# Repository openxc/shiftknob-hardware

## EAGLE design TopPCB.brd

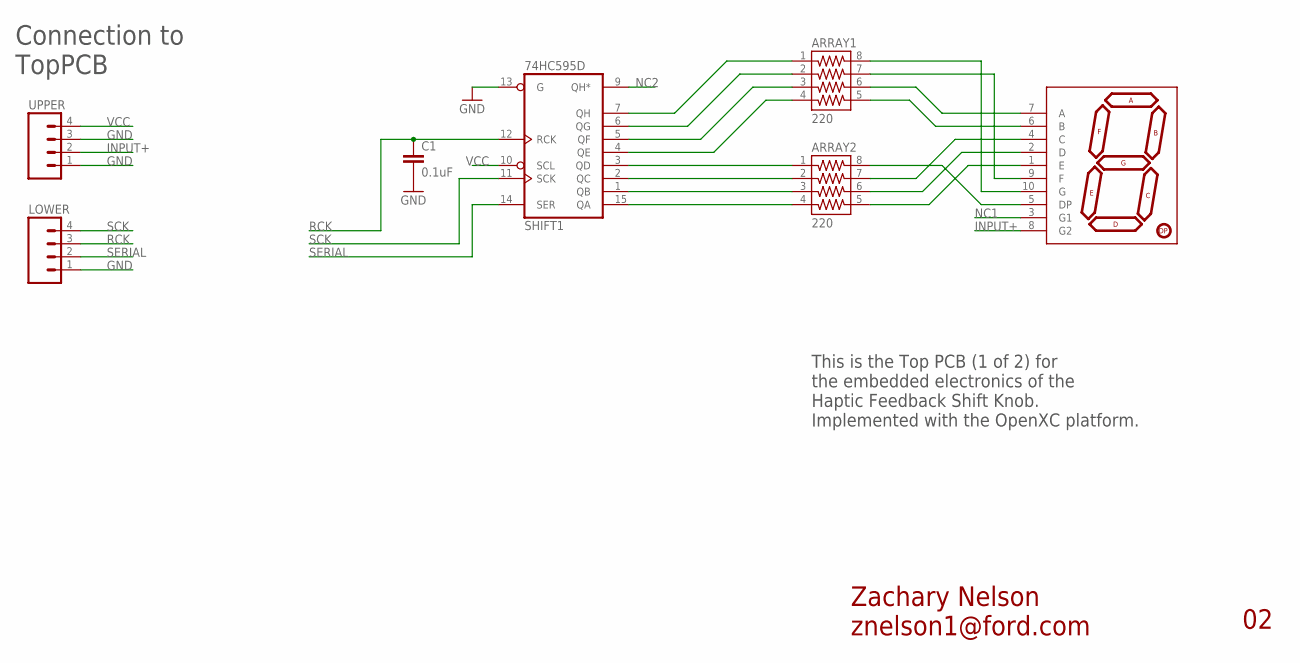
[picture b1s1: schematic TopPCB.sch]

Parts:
7SEGMENT: 7-SEGMENT-DISPLAY-1"-RED; 7-SEGMENT-1"PTH
ARRAY1, ARRAY2: 220; 744-8
C1: 0.1uF; 0402-CAP
LOWER: M04PTH; 1X04
SHIFT1: 74HC595D; SO16
UPPER: M04PTH; 1X04

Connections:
GND: C1.2, LOWER.1, SHIFT1.8 (GND), SHIFT1.13 (G), UPPER.1, UPPER.3
INPUT+: 7SEGMENT.8 (G2), UPPER.2
unnamed: 7SEGMENT.5 (DP), ARRAY2.8
unnamed: ARRAY2.3, SHIFT1.1 (QB)
unnamed: 7SEGMENT.1 (E), ARRAY2.5
unnamed: ARRAY2.2, SHIFT1.2 (QC)
unnamed: ARRAY2.1, SHIFT1.3 (QD)
unnamed: 7SEGMENT.4 (C), ARRAY2.7
unnamed: 7SEGMENT.6 (B), ARRAY1.5
unnamed: ARRAY2.4, SHIFT1.15 (QA)
unnamed: ARRAY1.4, SHIFT1.4 (QE)
unnamed: ARRAY1.3, SHIFT1.5 (QF)
unnamed: ARRAY1.2, SHIFT1.6 (QG)
unnamed: ARRAY1.1, SHIFT1.7 (QH)
unnamed: 7SEGMENT.7 (A), ARRAY1.6
unnamed: 7SEGMENT.9 (F), ARRAY1.7
unnamed: 7SEGMENT.10 (G), ARRAY1.8
unnamed: 7SEGMENT.2 (D), ARRAY2.6
NC1: 7SEGMENT.3 (G1)
NC2: SHIFT1.9 (QH*)
RCK: C1.1, LOWER.3, SHIFT1.12 (RCK)
SCK: LOWER.4, SHIFT1.11 (SCK)
SERIAL: LOWER.2, SHIFT1.14 (SER)
VCC: SHIFT1.10 (SCL), SHIFT1.16 (VCC), UPPER.4

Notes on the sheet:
Zachary Nelson znelson1@ford.com
This is the Top PCB (1 of 2) for the embedded electronics of the Haptic Feedback Shift Knob. Implemented with the OpenXC platform.
Connection to TopPCB

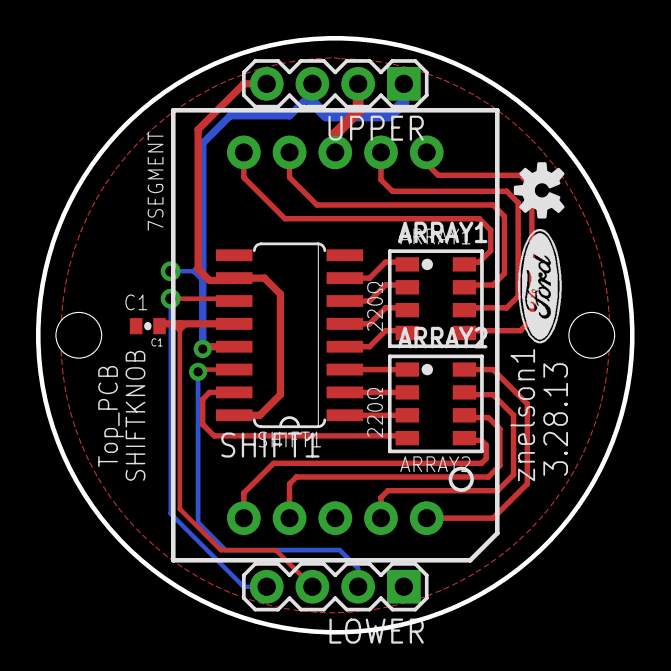
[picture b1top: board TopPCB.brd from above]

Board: 2 copper layers, 33.0 x 33.0 mm, 10 parts (1 on the bottom side), 22 nets.

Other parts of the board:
U$1, U$2: OSHW-LOGOS; OSHW-LOGO-S
U$3: DOCFIELD

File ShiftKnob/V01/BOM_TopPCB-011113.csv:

"Part";"Value";"Device";"Package";"Description";"";
"C1";"0.1uF";"CAP0402-CAP";"0402-CAP";"Capacitor";"";
"IC1";"74HC595D";"74HC595D";"SO16";"8-bit SHIFT REGISTER, output latch";"";
"JP1";"6 PIN 90degree Header";"M06POGOPIN_HOLES_ONLY";"1X06_HOLES_ONLY";"Header 6";"";
"RN1";"220";"744-8";"744-8";"CTS 744 Series";"";
"RN2";"220";"744-8";"744-8";"CTS 744 Series";"";
"U$1";"7-SEGMENT-DISPLAY-1"-RED";"7-SEGMENT-DISPLAY-1"-RED";"7-SEGMENT-1"PTH";"7-Segment Display 1" Red (COM-08546)";"";

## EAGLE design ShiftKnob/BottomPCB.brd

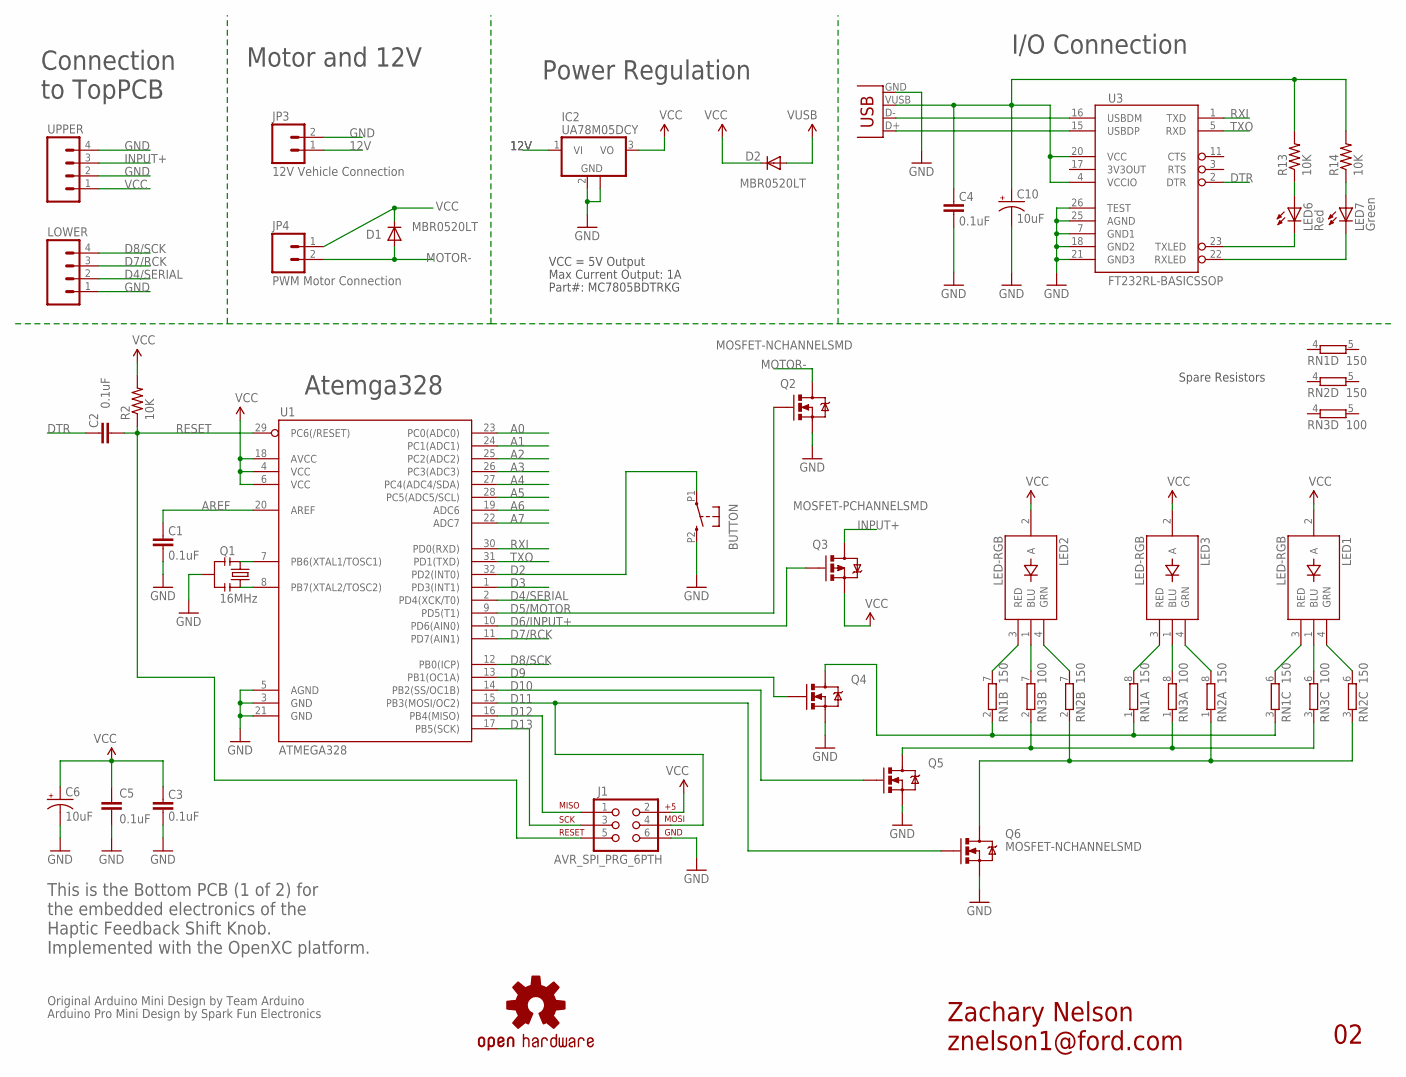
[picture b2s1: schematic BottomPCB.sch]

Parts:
BUTTON: BUTTON_EDGE
C1, C2, C3, C4, C5: 0.1uF; 0402-CAP
C6, C10: 10uF; EIA3216
D1, D2: MBR0520LT; SOD123
IC2: UA78M05DCY; SOT223
J1: AVR_SPI_PRG_6PTH; 2X3
JP3: 12V Vehicle Connection; 1X02
JP4: PWM Motor Connection; JST-2-SMD
LED1, LED2, LED3: LED-RGB; LED-RGB_SMD-RIGHTANGLE
LED6: Red; LED-0603
LED7: Green; LED-0603
LOWER: M04PTH; 1X04
Q1: 16MHz; RESONATOR-SMD
Q2, Q4, Q5, Q6: MOSFET-NCHANNELSMD; SOT23-3
Q3: MOSFET-PCHANNELSMD; SOT23-3
R2, R13, R14: 10K; 0402-RES
RN1, RN2: 150; EXBS8V
RN3: 100; EXBS8V
U1: ATMEGA328; TQFP32-08
U3: FT232RL-BASICSSOP; SSOP28DB
U6: USB-MINI-B_VERTICAL
U$3: OSHW-LOGOS; OSHW-LOGO-S
UPPER: M04PTH; 1X04

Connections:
12V: IC2.1 (VI), JP3.1
A0: U1.23 (PC0(ADC0))
A1: U1.24 (PC1(ADC1))
A2: U1.25 (PC2(ADC2))
A3: U1.26 (PC3(ADC3))
A4: U1.27 (PC4(ADC4/SDA))
A5: U1.28 (PC5(ADC5/SCL))
A6: U1.19 (ADC6)
A7: U1.22 (ADC7)
AREF: C1.2, U1.20 (AREF)
D2: BUTTON.P1 (1), U1.32 (PD2(INT0))
D3: U1.1 (PD3(INT1))
D4/SERIAL: LOWER.2, U1.2 (PD4(XCK/T0))
D5/MOTOR: Q2.1 (G), U1.9 (PD5(T1))
D6/INPUT+: Q3.1 (G), U1.10 (PD6(AIN0))
D7/RCK: LOWER.3, U1.11 (PD7(AIN1))
D8/SCK: LOWER.4, U1.12 (PB0(ICP))
D9: Q4.3 (D), RN1.1, RN1.2 (1), RN1.3 (1)
D10: Q5.3 (D), RN3.1, RN3.2 (1), RN3.3 (1)
D11: Q6.3 (D), RN2.1, RN2.2 (1), RN2.3 (1)
D12: J1.1, U1.16 (PB4(MISO))
D13: J1.3, U1.17 (PB5(SCK))
DTR: C2.2, U3.2 (DTR)
GND: BUTTON.P2 (2), C1.1, C3.1, C4.1, C5.2, C6.C (-), C10.C (-), IC2.2 (GND), IC2.4 (GND), J1.6, JP3.2, LOWER.1, Q1.2, Q2.2 (S), Q4.2 (S), Q5.2 (S), Q6.2 (S), U1.3 (GND), U1.5 (AGND), U1.21 (GND), U3.7 (GND1), U3.18 (GND2), U3.21 (GND3), U3.25 (AGND), U3.26 (TEST), U6.GND, UPPER.2, UPPER.4
INPUT+: Q3.3 (D), UPPER.3
MOTOR-: D1.A, JP4.2 (1), Q2.3 (D)
unnamed: Q1.1, U1.8 (PB7(XTAL2/TOSC2))
unnamed: Q1.3, U1.7 (PB6(XTAL1/TOSC1))
unnamed: LED2.3 (RED), RN1.7 (2)
unnamed: LED2.4 (GRN), RN2.7 (2)
unnamed: LED3.3 (RED), RN1.8 (2)
unnamed: LED1.1 (BLU), RN3.6 (2)
unnamed: LED3.4 (GRN), RN2.8 (2)
unnamed: LED1.3 (RED), RN1.6 (2)
unnamed: LED1.4 (GRN), RN2.6 (2)
unnamed: Q4.1 (G), U1.13 (PB1(OC1A))
unnamed: Q5.1 (G), U1.14 (PB2(SS/OC1B))
unnamed: J1.4, Q6.1 (G), U1.15 (PB3(MOSI/OC2))
unnamed: LED2.1 (BLU), RN3.7 (2)
unnamed: LED3.1 (BLU), RN3.8 (2)
unnamed: U3.15 (USBDP), U6.D+
unnamed: U3.16 (USBDM), U6.D-
unnamed: LED6.A, R13.1
unnamed: LED7.A, R14.1
RESET: C2.1, J1.5, R2.1, U1.29 (PC6(/RESET))
RXI: U1.30 (PD0(RXD)), U3.1 (TXD)
RXLED1: LED7.C, U3.22 (RXLED)
TXLED1: LED6.C, U3.23 (TXLED)
TXO: U1.31 (PD1(TXD)), U3.5 (RXD)
VCC: C3.2, C5.1, C6.A (+), D1.C, D2.C, IC2.3 (VO), J1.2, JP4.1 (2), LED1.2 (A), LED2.2 (A), LED3.2 (A), Q3.2 (S), R2.2, U1.4 (VCC), U1.6 (VCC), U1.18 (AVCC), UPPER.1
VUSB: C4.2, C10.A (+), D2.A, R13.2, R14.2, U3.4 (VCCIO), U3.20 (VCC), U6.VUSB (VBUS)

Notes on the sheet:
Zachary Nelson znelson1@ford.com
Original Arduino Mini Design by Team Arduino
Arduino Pro Mini Design by Spark Fun Electronics
Max Current Output: 1A
VCC = 5V Output
Part#: MC7805BDTRKG
Power Regulation
I/O Connection
Motor and 12V
Atemga328
Connection to TopPCB
This is the Bottom PCB (1 of 2) for the embedded electronics of the Haptic Feedback Shift Knob. Implemented with the OpenXC platform.
Spare Resistors

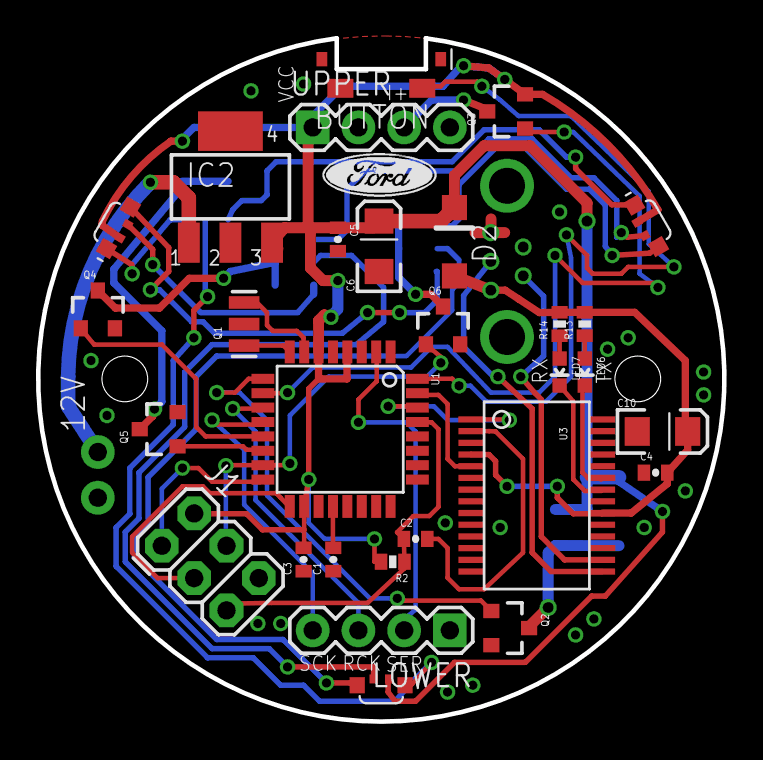
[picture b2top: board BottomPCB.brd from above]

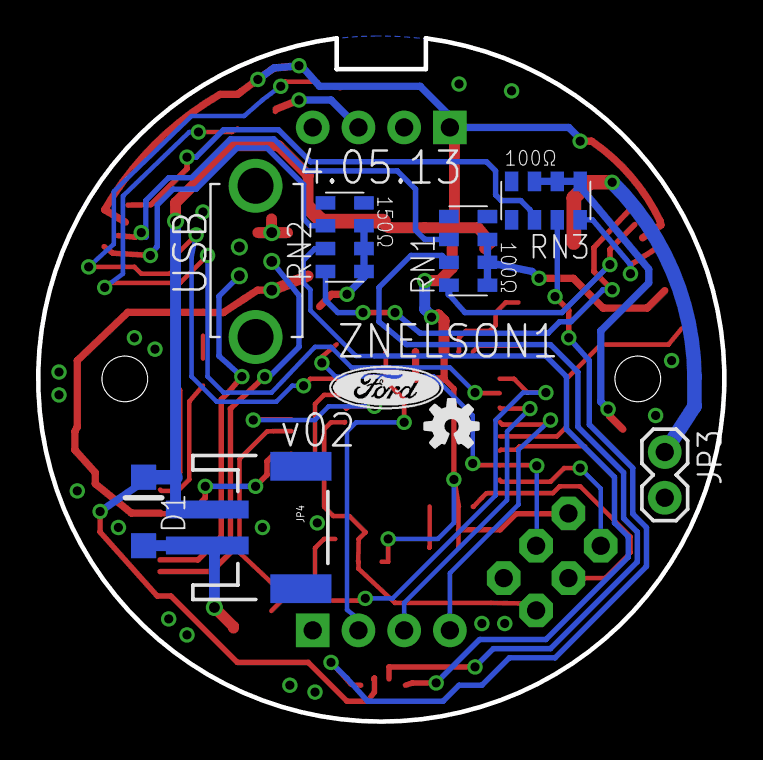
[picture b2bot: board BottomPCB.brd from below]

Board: 2 copper layers, 38.1 x 38.0 mm, 38 parts (8 on the bottom side), 42 nets.

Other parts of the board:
U$1: DOCFIELD

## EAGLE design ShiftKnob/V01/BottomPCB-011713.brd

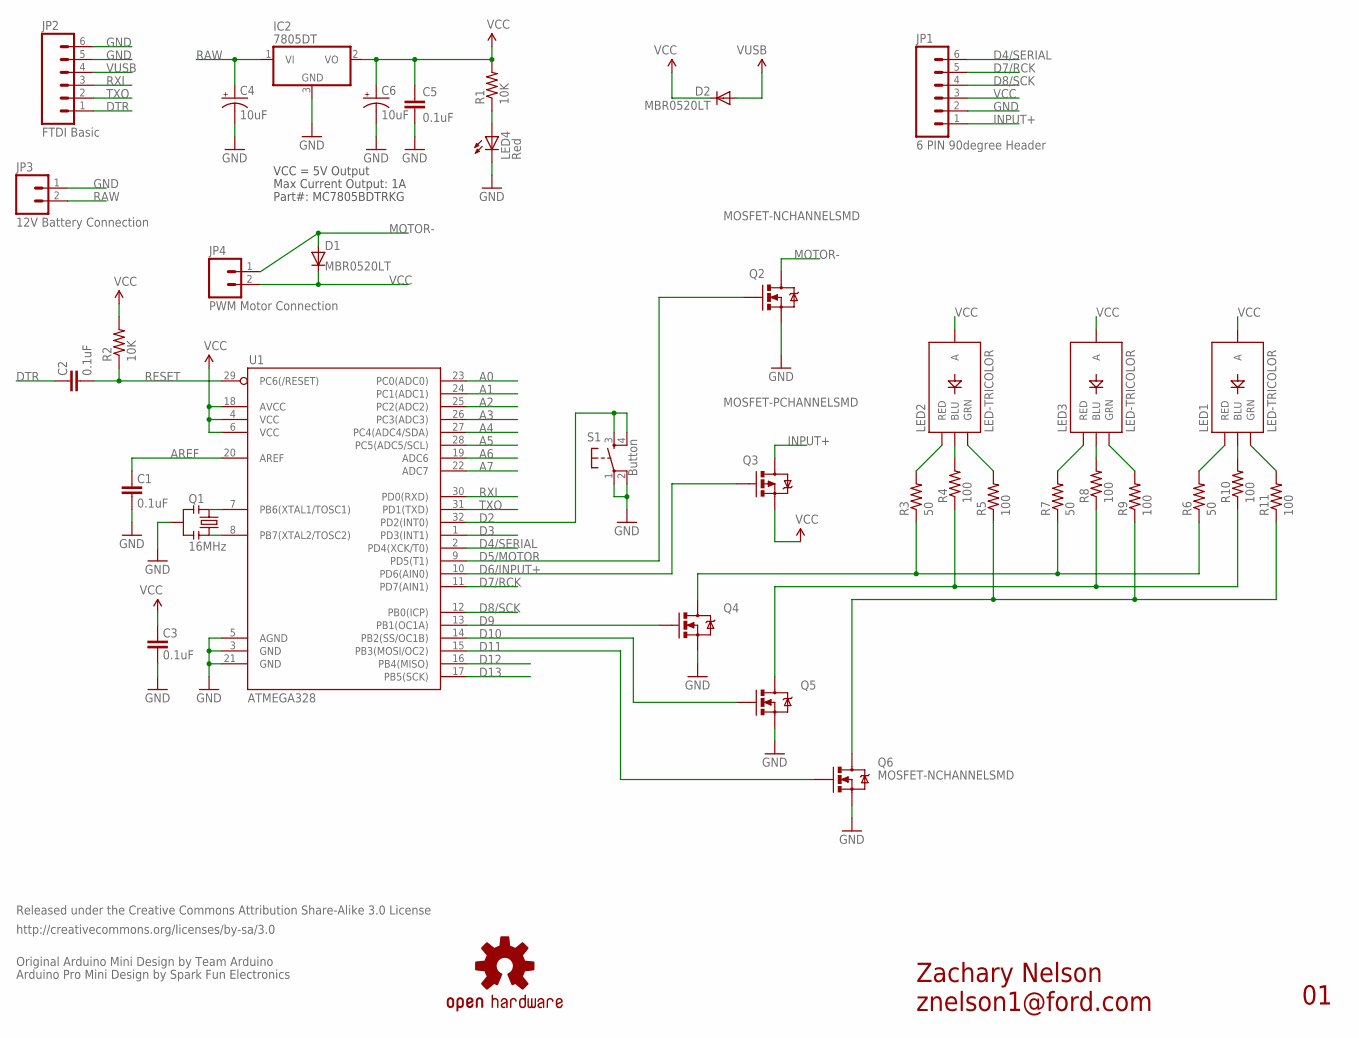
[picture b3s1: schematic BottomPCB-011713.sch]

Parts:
C1, C2, C3, C5: 0.1uF; 0402-CAP
C4, C6: 10uF; EIA3216
D1, D2: MBR0520LT; SOD123
IC2: 7805DT; TO252
JP1: 6 PIN 90degree Header; 1X06
JP2: FTDI Basic; 1X06
JP3: 12V Battery Connection; JST-2-SMD
JP4: PWM Motor Connection; JST-2-SMD
LED1, LED2, LED3: LED-TRICOLOR; LED-TRICOLOR-SMD
LED4: Red; LED-0603
Q1: 16MHz; RESONATOR-SMD
Q2, Q4, Q5, Q6: MOSFET-NCHANNELSMD; SOT23-3
Q3: MOSFET-PCHANNELSMD; SOT23-3
R1, R2: 10K; 0402-RES
R3, R6, R7: 50; 0805
R4, R5, R8, R9, R10, R11: 100; 0805
S1: Button; TACTILE_SWITCH_SMD
U1: ATMEGA328; TQFP32-08
U$3: OSHW-LOGOS; OSHW-LOGO-S

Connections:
A0: U1.23 (PC0(ADC0))
A1: U1.24 (PC1(ADC1))
A2: U1.25 (PC2(ADC2))
A3: U1.26 (PC3(ADC3))
A4: U1.27 (PC4(ADC4/SDA))
A5: U1.28 (PC5(ADC5/SCL))
A6: U1.19 (ADC6)
A7: U1.22 (ADC7)
AREF: C1.2, U1.20 (AREF)
D2: S1.3, S1.4, U1.32 (PD2(INT0))
D3: U1.1 (PD3(INT1))
D4/SERIAL: JP1.6, U1.2 (PD4(XCK/T0))
D5/MOTOR: Q2.1 (G), U1.9 (PD5(T1))
D6/INPUT+: Q3.1 (G), U1.10 (PD6(AIN0))
D7/RCK: JP1.5, U1.11 (PD7(AIN1))
D8/SCK: JP1.4, U1.12 (PB0(ICP))
D9: Q4.3 (D), R3.1, R6.1, R7.1
D10: Q5.3 (D), R4.1, R8.1, R10.1
D11: Q6.3 (D), R5.1, R9.1, R11.1
D12: U1.16 (PB4(MISO))
D13: U1.17 (PB5(SCK))
DTR: C2.2, JP2.1
GND: C1.1, C3.1, C4.C (-), C5.2, C6.C (-), IC2.3 (GND), JP1.2, JP2.5, JP2.6, JP3.1 (2), LED4.C, Q1.2, Q2.2 (S), Q4.2 (S), Q5.2 (S), Q6.2 (S), S1.1, S1.2, U1.3 (GND), U1.5 (AGND), U1.21 (GND)
INPUT+: JP1.1, Q3.3 (D)
MOTOR-: D1.A, JP4.1 (2), Q2.3 (D)
unnamed: Q1.1, U1.8 (PB7(XTAL2/TOSC2))
unnamed: Q1.3, U1.7 (PB6(XTAL1/TOSC1))
unnamed: LED4.A, R1.1
unnamed: LED2.R (RED), R3.2
unnamed: LED2.G (GRN), R5.2
unnamed: LED3.R (RED), R7.2
unnamed: LED1.B (BLU), R10.2
unnamed: LED3.G (GRN), R9.2
unnamed: LED1.R (RED), R6.2
unnamed: LED1.G (GRN), R11.2
unnamed: Q4.1 (G), U1.13 (PB1(OC1A))
unnamed: Q5.1 (G), U1.14 (PB2(SS/OC1B))
unnamed: Q6.1 (G), U1.15 (PB3(MOSI/OC2))
unnamed: LED3.B (BLU), R8.2
unnamed: LED2.B (BLU), R4.2
RAW: C4.A (+), IC2.1 (VI), JP3.2 (1)
RESET: C2.1, R2.1, U1.29 (PC6(/RESET))
RXI: JP2.3, U1.30 (PD0(RXD))
TXO: JP2.2, U1.31 (PD1(TXD))
VCC: C3.2, C5.1, C6.A (+), D1.C, D2.C, IC2.2 (VO), JP1.3, JP4.2 (1), LED1.A, LED2.A, LED3.A, Q3.2 (S), R1.2, R2.2, U1.4 (VCC), U1.6 (VCC), U1.18 (AVCC)
VUSB: D2.A, JP2.4

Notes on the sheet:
Zachary Nelson znelson1@ford.com
Released under the Creative Commons Attribution Share-Alike 3.0 License
http://creativecommons.org/licenses/by-sa/3.0
Original Arduino Mini Design by Team Arduino
Arduino Pro Mini Design by Spark Fun Electronics
Max Current Output: 1A
VCC = 5V Output
Part#: MC7805BDTRKG

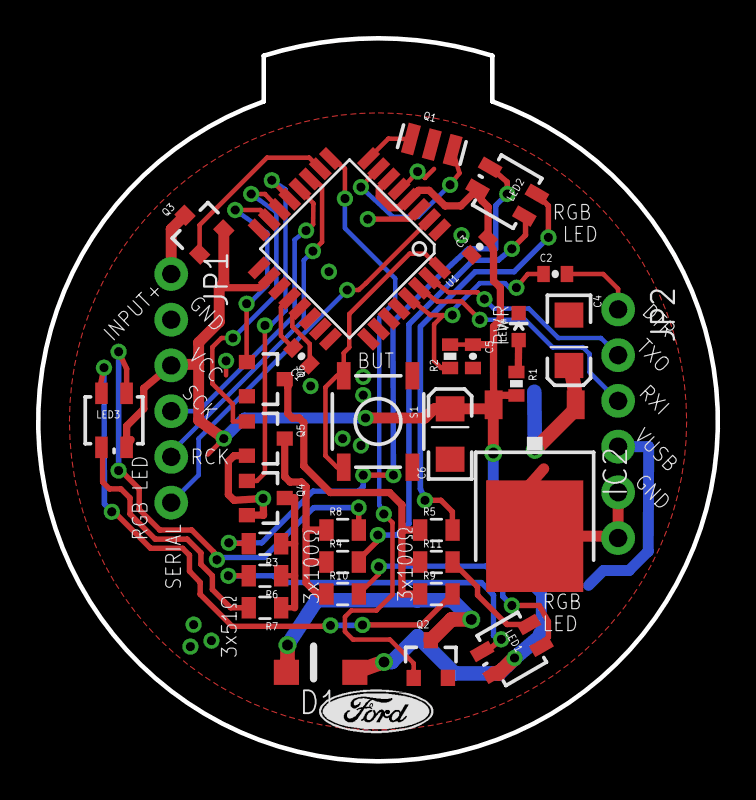
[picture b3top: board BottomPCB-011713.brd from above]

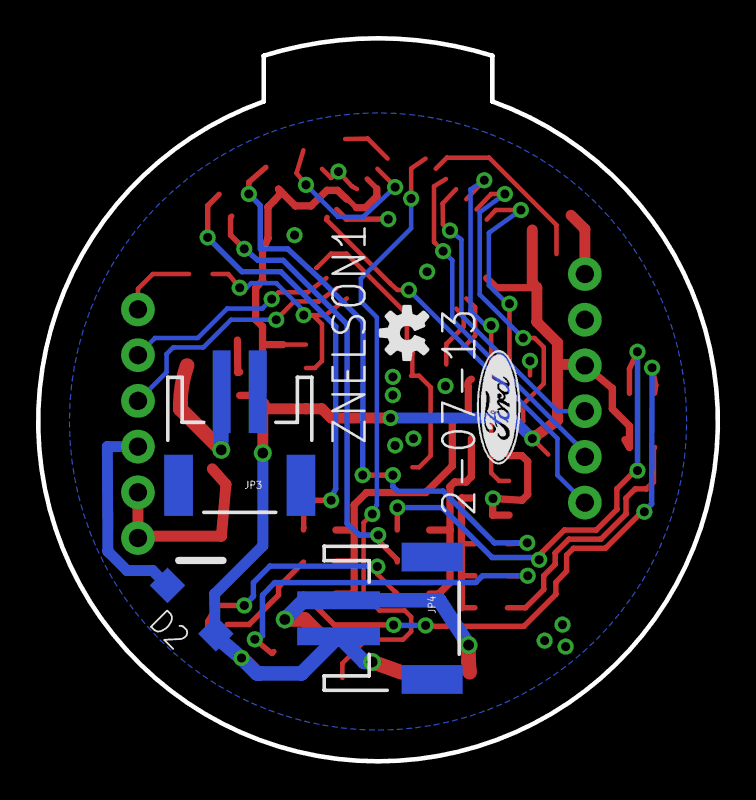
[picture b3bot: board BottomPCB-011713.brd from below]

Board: 2 copper layers, 37.8 x 40.2 mm, 37 parts (4 on the bottom side), 35 nets.

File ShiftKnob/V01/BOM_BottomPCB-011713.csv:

"Part";"Value";"Device";"Package";"Description";"PROD_ID";
"C1";"0.1uF";"CAP0402-CAP";"0402-CAP";"Capacitor";"";
"C2";"0.1uF";"CAP0402-CAP";"0402-CAP";"Capacitor";"";
"C3";"0.1uF";"CAP0402-CAP";"0402-CAP";"Capacitor";"";
"C4";"10uF";"CAP_POL1206";"EIA3216";"Capacitor Polarized";"";
"C5";"0.1uF";"CAP0402-CAP";"0402-CAP";"Capacitor";"";
"C6";"10uF";"CAP_POL1206";"EIA3216";"Capacitor Polarized";"";
"D1";"MBRA140";"MBRA140";"SMA-DIODE";"40V, 1A Schottky rectifier";"DIO-08053";
"D2";"MBR0520LT";"MBR0520LT";"SOD123";"SCHOTTKY BARRIER RECTIFIER";"";
"IC2";"7805DT";"7805DT";"TO252";"Positive VOLTAGE REGULATOR";"";
"JP1";"6 PIN 90degree Header";"M06SIP";"1X06";"Header 6";"";
"JP2";"FTDI Basic";"ARDUINO_SERIAL_PROGRAMPTH";"1X06";"";"";
"JP3";"12V Battery Connection";"M02-JST-2MM-SMT";"JST-2-SMD";"Header 2";"CONN-08352";
"JP4";"PWM Motor Connection";"M02-JST-2MM-SMT";"JST-2-SMD";"Header 2";"CONN-08352";
"LED1";"LED-TRICOLOR";"LED-TRICOLOR";"LED-TRICOLOR-SMD";"Tri-Color LED SMD";"";
"LED2";"LED-TRICOLOR";"LED-TRICOLOR";"LED-TRICOLOR-SMD";"Tri-Color LED SMD";"";
"LED3";"LED-TRICOLOR";"LED-TRICOLOR";"LED-TRICOLOR-SMD";"Tri-Color LED SMD";"";
"LED4";"Red";"LED0603";"LED-0603";"LEDs";"";
"Q1";"16MHz";"RESONATORSMD";"RESONATOR-SMD";"Resonator";"";
"Q2";"MOSFET-NCHANNELSMD";"MOSFET-NCHANNELSMD";"SOT23-3";"Generic NMOS footprint";"";
"Q3";"MOSFET-NCHANNELSMD";"MOSFET-NCHANNELSMD";"SOT23-3";"Generic NMOS footprint";"";
"Q4";"MOSFET-NCHANNELSMD";"MOSFET-NCHANNELSMD";"SOT23-3";"Generic NMOS footprint";"";
"Q5";"MOSFET-NCHANNELSMD";"MOSFET-NCHANNELSMD";"SOT23-3";"Generic NMOS footprint";"";
"Q6";"MOSFET-NCHANNELSMD";"MOSFET-NCHANNELSMD";"SOT23-3";"Generic NMOS footprint";"";
"R1";"10K";"RESISTOR0402-RES";"0402-RES";"Resistor";"";
"R2";"10K";"RESISTOR0402-RES";"0402-RES";"Resistor";"";
"R3";"50";"RESISTOR0805-RES";"0805";"Resistor";"";
"R4";"100";"RESISTOR0805-RES";"0805";"Resistor";"";
"R5";"100";"RESISTOR0805-RES";"0805";"Resistor";"";
"R6";"50";"RESISTOR0805-RES";"0805";"Resistor";"";
"R7";"50";"RESISTOR0805-RES";"0805";"Resistor";"";
"R8";"100";"RESISTOR0805-RES";"0805";"Resistor";"";
"R9";"100";"RESISTOR0805-RES";"0805";"Resistor";"";
"R10";"100";"RESISTOR0805-RES";"0805";"Resistor";"";
"R11";"100";"RESISTOR0805-RES";"0805";"Resistor";"";
"R12";"10k";"RESISTOR0402-RES";"0402-RES";"Resistor";"";
"S1";"Button";"TAC_SWITCHSMD";"TACTILE_SWITCH_SMD";"Momentary Switch";"";
"U$3";"OSHW-LOGOS";"OSHW-LOGOS";"OSHW-LOGO-S";"Open Source Hardware Logo This logo indicates the piece of hardware it is found on incorporates a OSHW license and/or adheres to the definition of open source hardware found here: http://freedomdefined.org/OSHW";"";
"U$11";"LOGO-SFENEW";"LOGO-SFENEW";"SFE-NEW-WEBLOGO";"Spark Fun Electronics PCB Logo";"";
"U1";"ATMEGA328";"ATMEGA168";"TQFP32-08";"";"";

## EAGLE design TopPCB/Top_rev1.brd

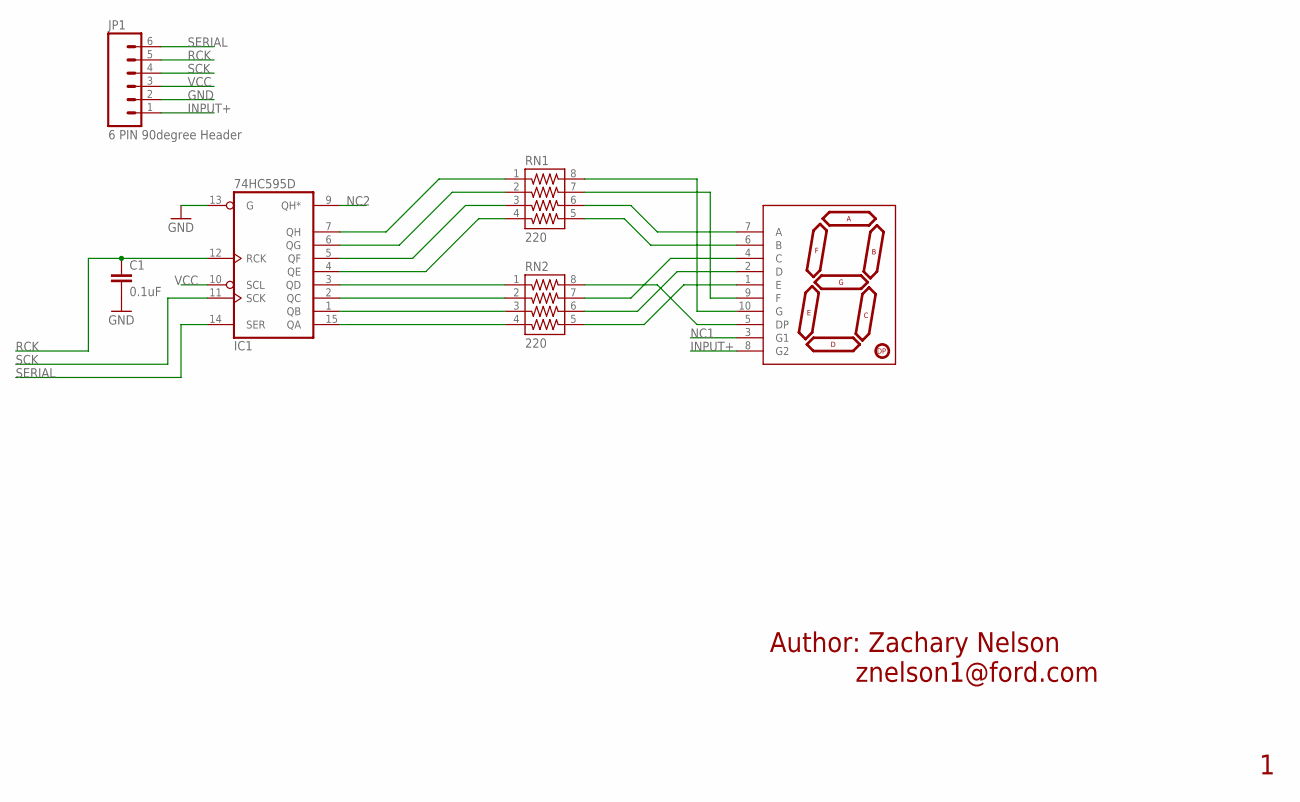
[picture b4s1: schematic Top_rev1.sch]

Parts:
C1: 0.1uF; 0402-CAP
IC1: 74HC595D; SO16
JP1: 6 PIN 90degree Header; 1X06_HOLES_ONLY
RN1, RN2: 220; 744-8
U$1: 7-SEGMENT-DISPLAY-1"-RED; 7-SEGMENT-1"PTH

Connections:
GND: C1.2, IC1.8 (GND), IC1.13 (G), JP1.2
INPUT+: JP1.1, U$1.8 (G2)
unnamed: RN2.8, U$1.5 (DP)
unnamed: IC1.1 (QB), RN2.3
unnamed: RN2.5, U$1.1 (E)
unnamed: IC1.2 (QC), RN2.2
unnamed: IC1.3 (QD), RN2.1
unnamed: RN2.7, U$1.4 (C)
unnamed: RN1.5, U$1.6 (B)
unnamed: IC1.15 (QA), RN2.4
unnamed: IC1.4 (QE), RN1.4
unnamed: IC1.5 (QF), RN1.3
unnamed: IC1.6 (QG), RN1.2
unnamed: IC1.7 (QH), RN1.1
unnamed: RN1.6, U$1.7 (A)
unnamed: RN1.7, U$1.9 (F)
unnamed: RN1.8, U$1.10 (G)
unnamed: RN2.6, U$1.2 (D)
NC1: U$1.3 (G1)
NC2: IC1.9 (QH*)
RCK: C1.1, IC1.12 (RCK), JP1.5
SCK: IC1.11 (SCK), JP1.4
SERIAL: IC1.14 (SER), JP1.6
VCC: IC1.10 (SCL), IC1.16 (VCC), JP1.3

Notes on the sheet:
Author: Zachary Nelson znelson1@ford.com

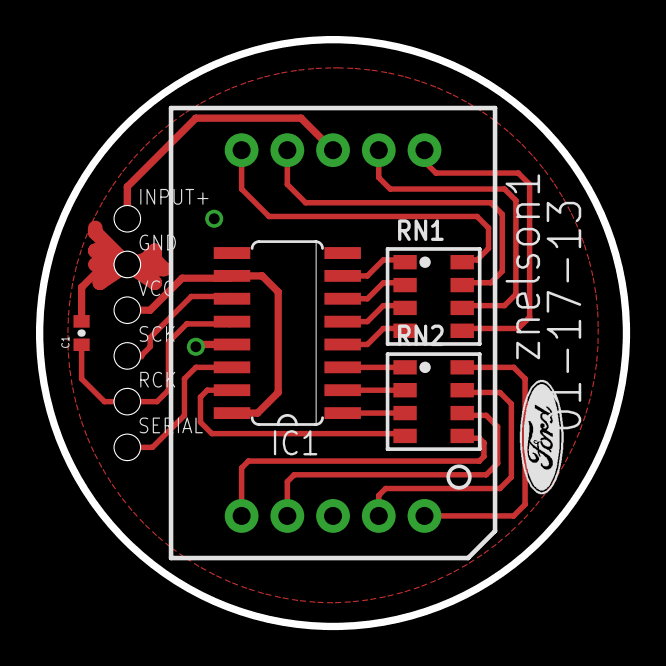
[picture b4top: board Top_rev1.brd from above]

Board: 2 copper layers, 32.6 x 32.6 mm, 6 parts (0 on the bottom side), 22 nets.

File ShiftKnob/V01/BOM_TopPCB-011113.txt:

Partlist exported from C:/cygwin/home/znelson1/projects/shiftknob-schematics/ShiftKnob/V01/TopPCB-011113.sch at 1/28/2013 11:59:41 AM

Part     Value                    Device                   Package         Description                          
7SEGMENT 7-SEGMENT-DISPLAY-1"-RED 7-SEGMENT-DISPLAY-1"-RED 7-SEGMENT-1"PTH 7-Segment Display 1" Red (COM-08546) 
ARRAY1   220                      744-8                    744-8           CTS 744 Series                       
ARRAY2   220                      744-8                    744-8           CTS 744 Series                       
C1       0.1uF                    CAP0402-CAP              0402-CAP        Capacitor                            
JP1      6 PIN 90degree Header    M06POGOPIN_HOLES_ONLY    1X06_HOLES_ONLY Header 6                             
SHIFT1   74HC595D                 74HC595D                 SO16            8-bit SHIFT REGISTER, output latch

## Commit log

2013-01-04 initial BOM commit
2013-01-14 creating project folders
2013-01-14 added all components and connections for Top PCB.
2013-01-15 add .b#* and .s#* to .gitignore
2013-01-15 layout board and route traces. changed a few signals between shift register and 7 segment
2013-01-15 remove ground connection on pin 9 of shift register
2013-01-18 remove BottomPCB folder, finished version 1 of TopPCB, moved Bottom_rev1 to TopPCB folder, first commit of Bottom pcb work.
2013-01-18 change folder/file structure to match SVL PCB guidelines
2013-01-18 more folder/file changes to match SVL PCB guidelines
2013-01-18 all components added to BottomPCB schematic. added: MOSFETs, RGB LEDs x2, Motor connector, 7805 regulator
2013-01-18 change battery and motor connectors to SMT parts
2013-01-18 add 1 more RGB led. add FETs for controlling 3 LEDs.
2013-01-18 switch pins on battery connector and motor connector to match footprint
2013-01-18 all components on the board with no traces
2013-01-22 add .pro to gitignore. Its just a file of autotrace statistics
2013-01-22 add pullup resistor to button. adding traces to board.
2013-01-22 minor board adjustment. increase trace width of Vcc.
2013-01-22 add more traces to brd layout. not yet finished.
2013-01-23 add schottky diode to hand usb power auto selection
2013-01-23 all traces done except ground.
2013-01-24 all traces complete. all GND pins connected and clear.
2013-01-24 increase diameter of board to 33 mm
2013-01-24 add BOM files.
2013-01-24 remove centerline
2013-01-25 add gnd trace on bottom layer. increase width of input+
2013-01-25 name components, add silk screen labels, copy name-date-logo to bottom layer, increase board diameter to 33mm
2013-01-25 increase isolation on ground pour. move labels
2013-01-25 add open hardware logo
2013-01-25 preliminarily finalized. added silk screen labels. may still add mounting holes
2013-01-25 minor tweak
2013-01-28 redo outer boundary of board. increase overall size and add locating features for housing integration.
2013-01-28 add Ford logo to the top of the board.
2013-01-28 remove csv BOM and resave as .txt
2013-01-28 adjust silk screen for vector font.
2013-01-28 adjust silk screen layer for large font size.
2013-01-28 run DRC test and fix all issues.
2013-01-29 change 6 pin connector to match bottomPCB. run DRC and correct issues. move dimension callout to Document layer.
2013-01-29 commit of V01 fab files
2013-01-29 change diodes to match. add silk screen for polarity marking.
2013-01-29 initial commit of excel BOMs
2013-01-29 redo Gerber files. with changed components and added silk screens.
2013-01-30 move molex connectors on board to allow for better spacing. regenerate gerber files.
2013-01-30 resize board perimeter. redo fab files.
2013-01-30 changed the outer board perimeter one last time. V01 of bottom board finalized. regenerated fab files.
2013-02-01 minor change to BOM.
2013-02-01 change border thickenss to .008"
2013-02-02 initial commit of changeOrder.
2013-02-02 add to changeOrder: remove pull-up resistor on button and use internal pullup resistor on atmega328
2013-02-07 attach button to arduino pin 2 rather than 12 to use internal interrupt. adjust board accordingly. remove resistor and use internal resistor of atemga328.
2013-02-07 change fab file zip folder names to include the date the folders were created.
2013-02-07 final Gerber file generation for V01 with button interrupt pin change.
2013-02-07 change outer profile to be .010 to match BatchPCB DRC check.
2013-02-07 regenerate gerber files for top board. update change order. all changes made.
2013-02-08 final finalized versions of boards and fab files.
2013-02-14 fix board layout and schematic to properly setup MOSFETs. regenerate Gerber files. Change N-Channel MOSFET to P-Channel for 7segment brightness control (INPUT+)
2013-02-14 add Pchannel SMD MOSFET to BOM.
2013-02-27 update schematics with new Ford frame.
2013-03-12 update with new frames and printed drawings for assembly.
2013-03-19 update everything before moving on to V02.
2013-03-19 remove unneeded files.
2013-03-19 move all files up one directory for shiftKnob PCBs. use tags for versioning rather than folders.
2013-03-19 remove time stamp from file names
2013-03-20 add ICSP 6-pin header to schematic.
2013-03-20 fixed silk screen marking for motor diode.
2013-03-20 change red LED resistance from 50ohm to 100ohm.
2013-03-20 remove power LED and resistor. not needed as RGB leds turn on when 5V is applied during startup.
2013-03-21 finish the schematic for the FTDI chip. Need to rework the board layout still.
2013-03-22 switch out RGB LEDs for Right-Angle RGBs from FORD_frames library. Still need to fix layout.
2013-03-26 add resistor arrays. clear off board layout and begin moving components.
2013-03-27 bring up to date. schematic almost finalized.
2013-03-28 add right angle button to schematic.
2013-03-28 update changeOrder
2013-03-28 move C1, add (2) 0.1in holes for assembly and rework silk screens. move PCB to be centered at .85x.85 like bottomPCB
2013-03-28 use (2) 4 pin connectors rather than a 6 pin connector. Board layout and schematic preliminarily complete.
2013-04-01 add 0.1" holes in bottom PCB.
2013-04-01 redo silk screen pin labels. DRC checks out OK.
2013-04-01 remove 6 pin header. add (2) 4 pin headers and place in the correct location to match TopPCB.
2013-04-01 swap out button for edge_mount button in Ford_frames library.
2013-04-02 remove eagle.epf from tracked files. I think this just sets up the relevant libraries needed for the project, but the file locations different between computers.
2013-04-02 everything on the board. need to route traces.
2013-04-03 reworked the board layout. power traces complete.
2013-04-04 fix VCC connection on RGB LEDs. Connection was not previously made between pin2 and VCC on each LED.
2013-04-04 change 12V connection to 2 through hole solder points.
2013-04-04 swap pins on button for easier board layout.
2013-04-04 all traces done except motor connection and RGB LEDs.
2013-04-05 swap pins on motor connection. add junctions where necessary. reorganize resistors for easier board layout.
2013-04-05 board layout done. DRC check complete and all errors fixed. Only silk screens remaining.
2013-04-05 Bottom board layout is finalized. 1st attempt at generating gerber files failed BatchPCB test.
2013-04-08 updated ground plane to pass DRC bot in BatchPCB. Gerber files generated for Top and Bottom. Everything passed BatchPCB test.
2013-04-08 update BOMs with all components for v02
2013-04-08 move silk screens for better visibility.
2013-04-18 add v02 and v01 docs.
2013-04-29 add new change log for v02.
2013-05-29 fix TX/RX issue on v02 board schematic and layout.
2013-05-29 fix board layout to match OSH Park DRU check. regenerate gerber files including the new .GKO outline file needed for OSH.
2013-06-05 update BOM.
2013-06-10 update BOMs.
2013-06-11 remove Arduino Pro Mini design files.
2013-06-11 remove intial BOM. Out of date and not needed.
2013-06-11 cleanup Fab_files and remove unneccesary files.
2013-06-11 add v01 and v02 build files to docs.
2013-06-11 update change order for v02. remove change order for v01.
2013-06-11 remove unneccesary file.
2013-06-11 update doc pdfs with minor v02 changes.
2013-06-11 Move everything to the top level.
2013-06-11 initial commit of README.
2013-06-11 change readme filename to README.mkd.
2013-06-11 fix links in Resources.
2013-06-11 change license to CC.
2013-06-11 fix typo for PCB BOMs.
2013-06-13 Add CC LICENSE text file.
2013-06-13 Wrap lines in README at 80 chars.
2013-06-13 Fix typo in README.

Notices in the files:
parts and their libraries:
SparkFun-Connectors: Licensing: CC v3.0 Share-Alike You are welcome to use this library for commercial purposes.
resistor-array: Copyright (C) 2008, Bob Starr
